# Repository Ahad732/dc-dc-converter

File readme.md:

# dc-dc converter
i have made a DC-DC Converter it gives 5v output to any input voltage . its like a buck converter but for a fixed output vloltage. i used LMR33630 ic for it.I copied it from a on paper schematic that i made and also added some changes.

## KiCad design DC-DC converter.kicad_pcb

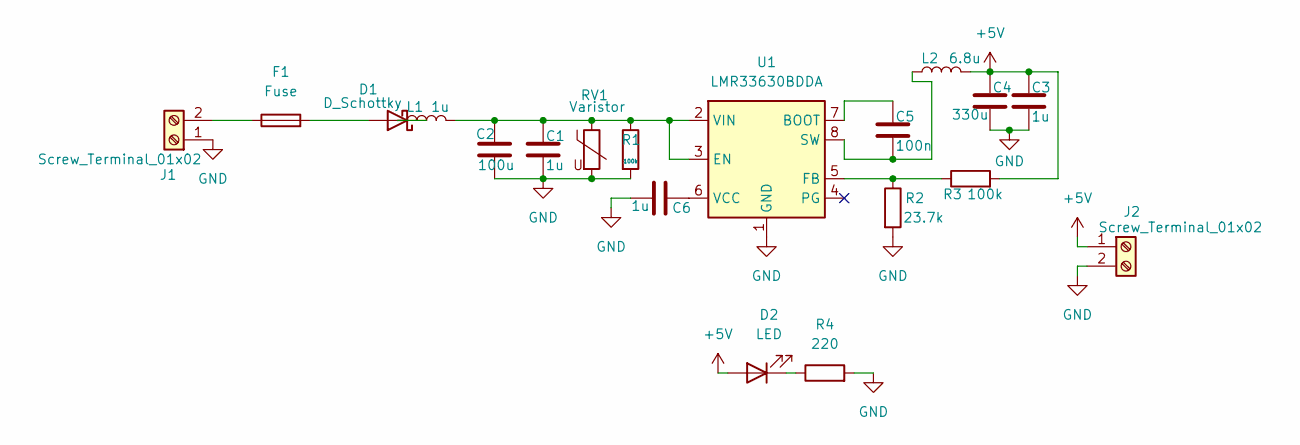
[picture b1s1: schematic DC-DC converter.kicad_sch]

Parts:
C1, C3, C6: 1u; C_1206_3216Metric
C2: 100u; CP_Radial_D6.3mm_P2.50mm
C4: 330u; CP_Radial_D10.0mm_P5.00mm
C5: 100n; C_1206_3216Metric
D1: D_Schottky; D_SMA
D2: LED; LED_0402_1005Metric
F1: Fuse; Fuse_1206_3216Metric
J1, J2: Screw_Terminal_01x02; TerminalBlock_MaiXu_MX126-5.0-02P_1x02_P5.00mm
L1: 1u; L_1008_2520Metric
L2: 6.8u; L_7.3x7.3_H3.5
R1, R3: 100k; R_0402_1005Metric
R2: 23.7k; R_0402_1005Metric
R4: 220; R_0402_1005Metric
RV1: Varistor; RV_Disc_D7mm_W3.4mm_P5mm
U1: LMR33630BDDA; Texas_HSOP-8-1EP_3.9x4.9mm_P1.27mm_ThermalVias

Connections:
+5V: C3.1, C4.1, D2.2 (A), J2.1, L2.2, R3.2
GND: C1.2, C2.2, C3.2, C4.2, C6.2, J1.1, J2.2, R1.2, R2.2, R4.2, RV1.2, U1.1 (GND), U1.9 (GND)
unnamed: D1.2 (A), F1.2
unnamed: D1.1 (K), L1.1
unnamed: D2.1 (K), R4.1
unnamed: F1.1, J1.2
unnamed: C5.1, U1.7 (BOOT)
unnamed: C1.1, C2.1, L1.2, R1.1, RV1.1, U1.2 (VIN), U1.3 (EN)
unnamed: R2.1, R3.1, U1.5 (FB)
unnamed: C5.2, L2.1, U1.8 (SW)
unnamed: C6.1, U1.6 (VCC)

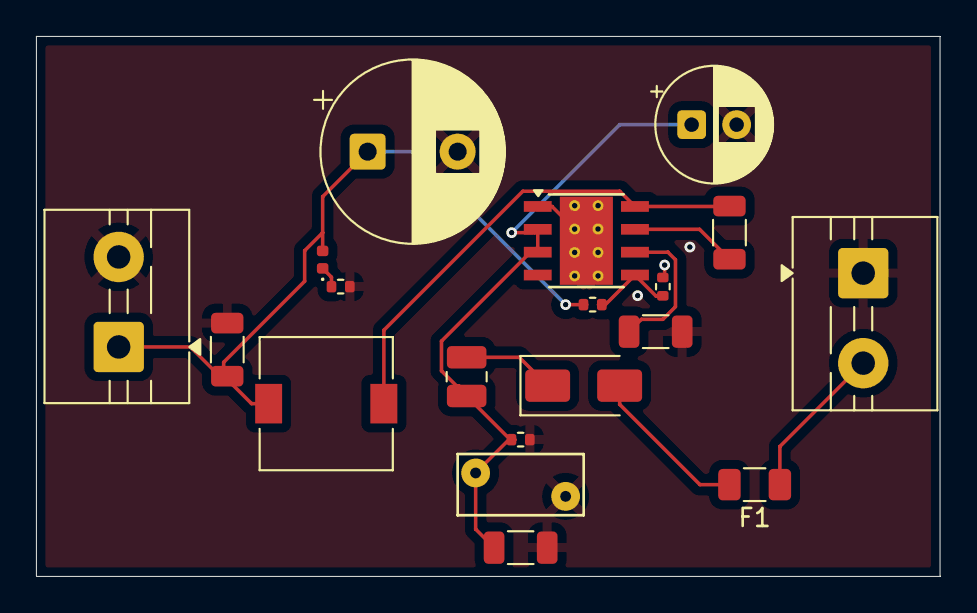
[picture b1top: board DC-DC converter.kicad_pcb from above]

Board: 2 copper layers, 50.2 x 30.0 mm, 19 parts (0 on the bottom side), 11 nets.

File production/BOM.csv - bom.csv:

Designator,Footprint,Quantity,Value,Link,Price
"C1, C3, C6",1206,50,1u,https://www.lcsc.com/product-detail/C5187282.html,0.67
C2,CP_Radial_D6.3mm_P2.50mm,20,100u,https://www.lcsc.com/product-detail/C52994849.html,0.66
C4,CP_Radial_D10.0mm_P5.00mm,10,330u,https://www.lcsc.com/product-detail/C49332876.html,0.23
C5,1206,20,100n,https://www.lcsc.com/product-detail/C24497.html,0.44
D1,D_SMA,20,D_Schottky,https://www.lcsc.com/product-detail/C7470651.html,0.65
D2,402,50,LED,https://www.lcsc.com/product-detail/C51933302.html,0.4
F1,1206,10,Fuse,https://www.lcsc.com/product-detail/C41367227.html,0.5
"J1, J2",TerminalBlock_MaiXu_MX126-5.0-02P_1x02_P5.00mm,5,Screw_Terminal_01x02,https://www.lcsc.com/product-detail/C474881.html,0.5
L1,1008,20,1u,https://www.lcsc.com/product-detail/C42455356.html,0.68
L2,L_7.3x7.3_H3.5,5,6.8u,https://www.lcsc.com/product-detail/C718267.html,0.14
"R1, R3",402,100,100k,https://www.lcsc.com/product-detail/C60491.html,0.14
R2,402,100,23.7k,https://www.lcsc.com/product-detail/C327362.html,0.14
R4,402,100,220,https://www.lcsc.com/product-detail/C2909336.html,0.16
RV1,RV_Disc_D7mm_W3.4mm_P5mm,20,Varistor,https://www.lcsc.com/product-detail/C22390607.html,0.32
U1,Texas_HSOP-8-1EP_3.9x4.9mm_P1.27mm_ThermalVias,1,LMR33630BDDA,https://www.lcsc.com/product-detail/C544370.html,0.74
,,,,PCB + PCB Shipping,9.98
,,,,Parts Shipping,8.78
,,,,Total,25.13

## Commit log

2026-06-28 made the readme
2026-06-28 Added Images
2026-06-28 Added new updated BOM
2026-06-28 submitting
